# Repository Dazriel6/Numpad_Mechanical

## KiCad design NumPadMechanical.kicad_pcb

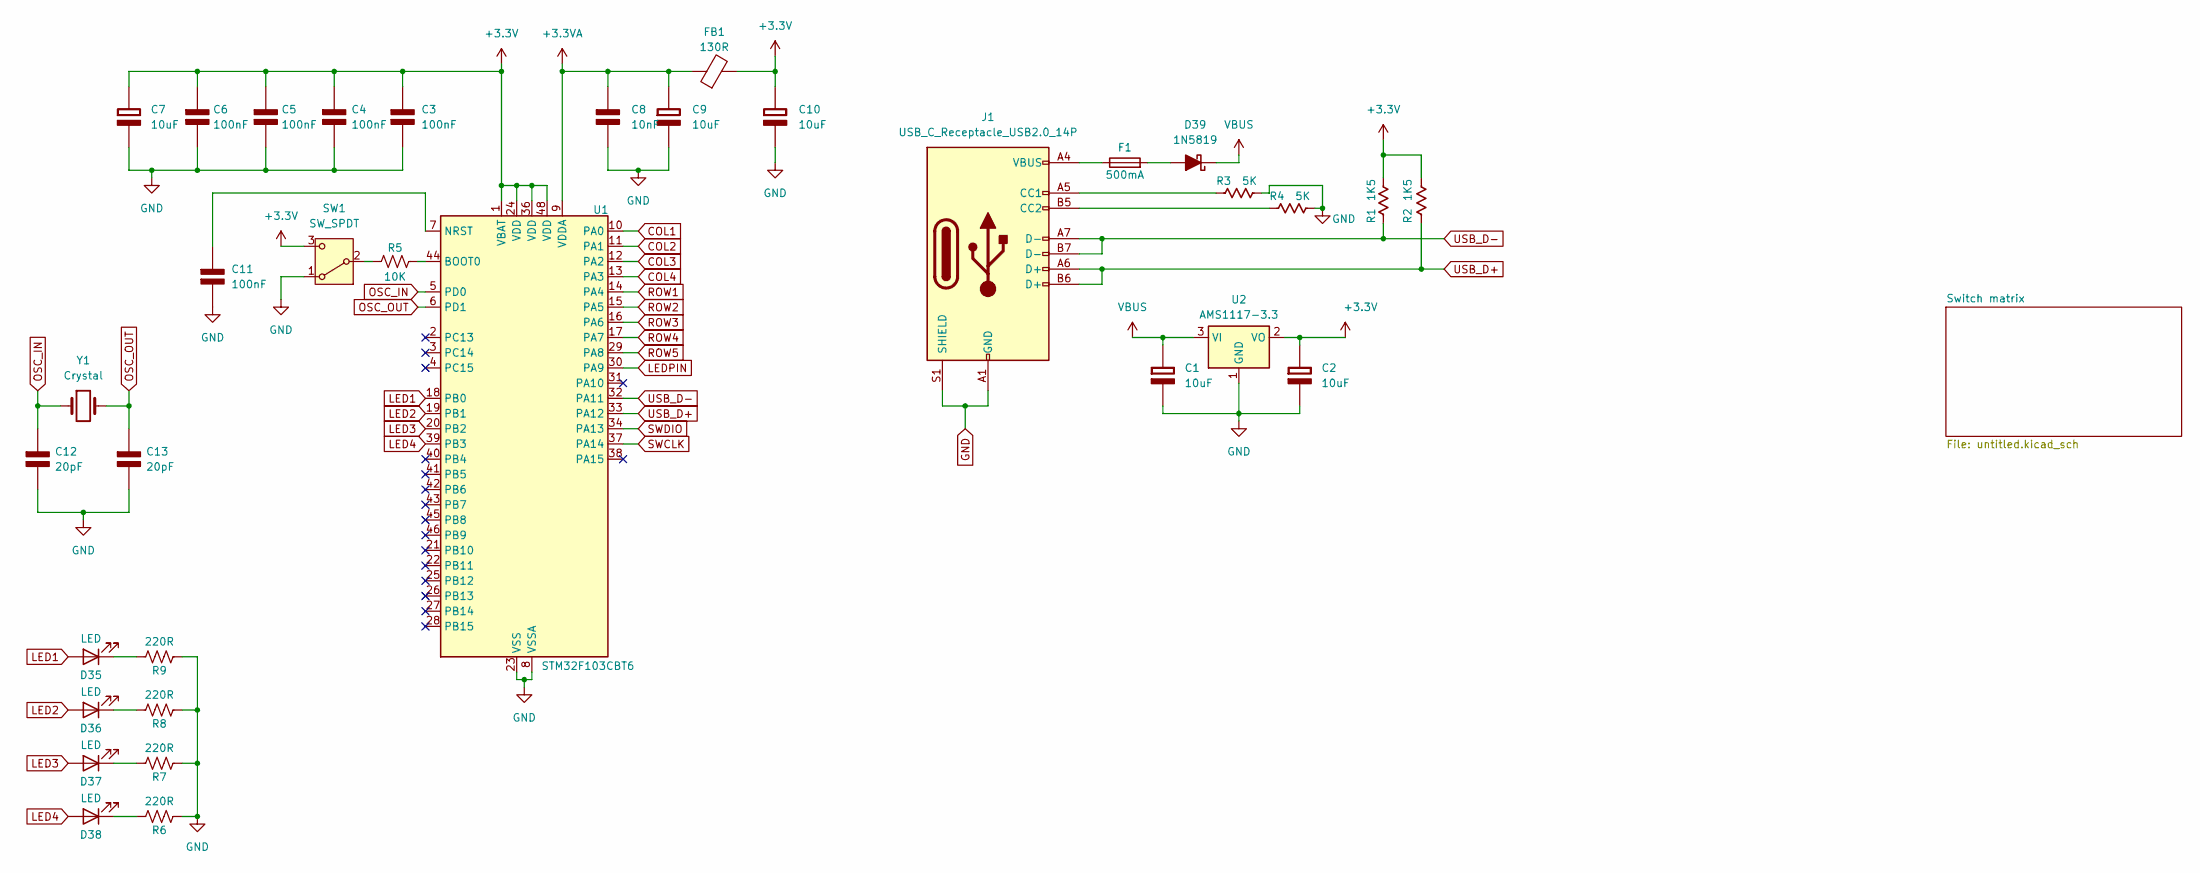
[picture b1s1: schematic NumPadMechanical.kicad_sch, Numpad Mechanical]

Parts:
C1, C2, C7, C9, C10: 10uF; C_0603_1608Metric; Rating V
C3, C4, C5, C6, C11: 100nF; C_0603_1608Metric_Pad1.08x0.95mm_HandSolder; Rating V
C8: 10nF; C_0603_1608Metric; Rating V
C12, C13: 20pF; C_0603_1608Metric_Pad1.08x0.95mm_HandSolder; Rating V
D35, D36, D37, D38: LED; LED_0603_1608Metric
D39: 1N5819; D_SOD-123_A
F1: 500mA; Fuse_0603_1608Metric
FB1: 130R; L_0603_1608Metric
J1: USB_C_Receptacle_USB2.0_14P; USB_C_Receptacle_XKB_U262-16XN-4BVC11
R1, R2: 1K5; R_0603_1608Metric
R3, R4: 5K; R_0603_1608Metric
R5: 10K; R_0603_1608Metric
R6, R7, R8, R9: 220R; R_0603_1608Metric
SW1: SW_SPDT; SW_Slide_SPDT_Straight_CK_OS102011MS2Q
U1: STM32F103CBT6; LQFP-48_7x7mm_P0.5mm
U2: AMS1117-3.3; SOT-223-3_TabPin2
Y1: Crystal; Crystal_SMD_HC49-SD

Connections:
+3.3V: C2.1 (+), C3.1 (+), C4.1 (+), C5.1 (+), C6.1 (+), C7.1 (+), C10.1 (+), FB1.2, R1.2, R2.2, SW1.3 (C), U1.1 (VBAT), U1.24 (VDD), U1.36 (VDD), U1.48 (VDD), U2.2 (VO)
+3.3VA: C8.1 (+), C9.1 (+), FB1.1, U1.9 (VDDA)
COL1: U1.10 (PA0); also elsewhere on the board
COL2: U1.11 (PA1); also elsewhere on the board
COL3: U1.12 (PA2); also elsewhere on the board
COL4: U1.13 (PA3); also elsewhere on the board
GND: C1.2 (-), C2.2 (-), C3.2 (-), C4.2 (-), C5.2 (-), C6.2 (-), C7.2 (-), C8.2 (-), C9.2 (-), C10.2 (-), C11.2 (-), C12.2 (-), C13.2 (-), J1.A1 (GND), J1.A12 (GND), J1.B1 (GND), J1.B12 (GND), J1.S1 (SHIELD), R3.2, R4.2, R6.2, R7.2, R8.2, R9.2, SW1.1 (A), U1.8 (VSSA), U1.23 (VSS), U1.35 (VSS), U1.47 (VSS), U2.1 (GND); also elsewhere on the board
LED1: D35.2 (A), U1.18 (PB0)
LED2: D36.2 (A), U1.19 (PB1)
LED3: D37.2 (A), U1.20 (PB2)
LED4: D38.2 (A), U1.39 (PB3)
LEDPIN: U1.30 (PA9); also elsewhere on the board
unnamed: C11.1 (+), U1.7 (NRST)
unnamed: D35.1 (K), R9.1
unnamed: D36.1 (K), R8.1
unnamed: D37.1 (K), R7.1
unnamed: D38.1 (K), R6.1
unnamed: D39.2 (A), F1.2
unnamed: F1.1, J1.A4 (VBUS), J1.A9 (VBUS), J1.B4 (VBUS), J1.B9 (VBUS)
unnamed: J1.A5 (CC1), R3.1
unnamed: J1.B5 (CC2), R4.1
unnamed: R5.2, SW1.2 (B)
unnamed: R5.1, U1.44 (BOOT0)
OSC_IN: C12.1 (+), U1.5 (PD0), Y1.1
OSC_OUT: C13.1 (+), U1.6 (PD1), Y1.2
ROW1: U1.14 (PA4); also elsewhere on the board
ROW2: U1.15 (PA5); also elsewhere on the board
ROW3: U1.16 (PA6); also elsewhere on the board
ROW4: U1.17 (PA7); also elsewhere on the board
ROW5: U1.29 (PA8); also elsewhere on the board
SWCLK: U1.37 (PA14)
SWDIO: U1.34 (PA13)
USB_D+: J1.A6 (D+), J1.B6 (D+), R2.1, U1.33 (PA12)
USB_D-: J1.A7 (D-), J1.B7 (D-), R1.1, U1.32 (PA11)
VBUS: C1.1 (+), D39.1 (K), U2.3 (VI)

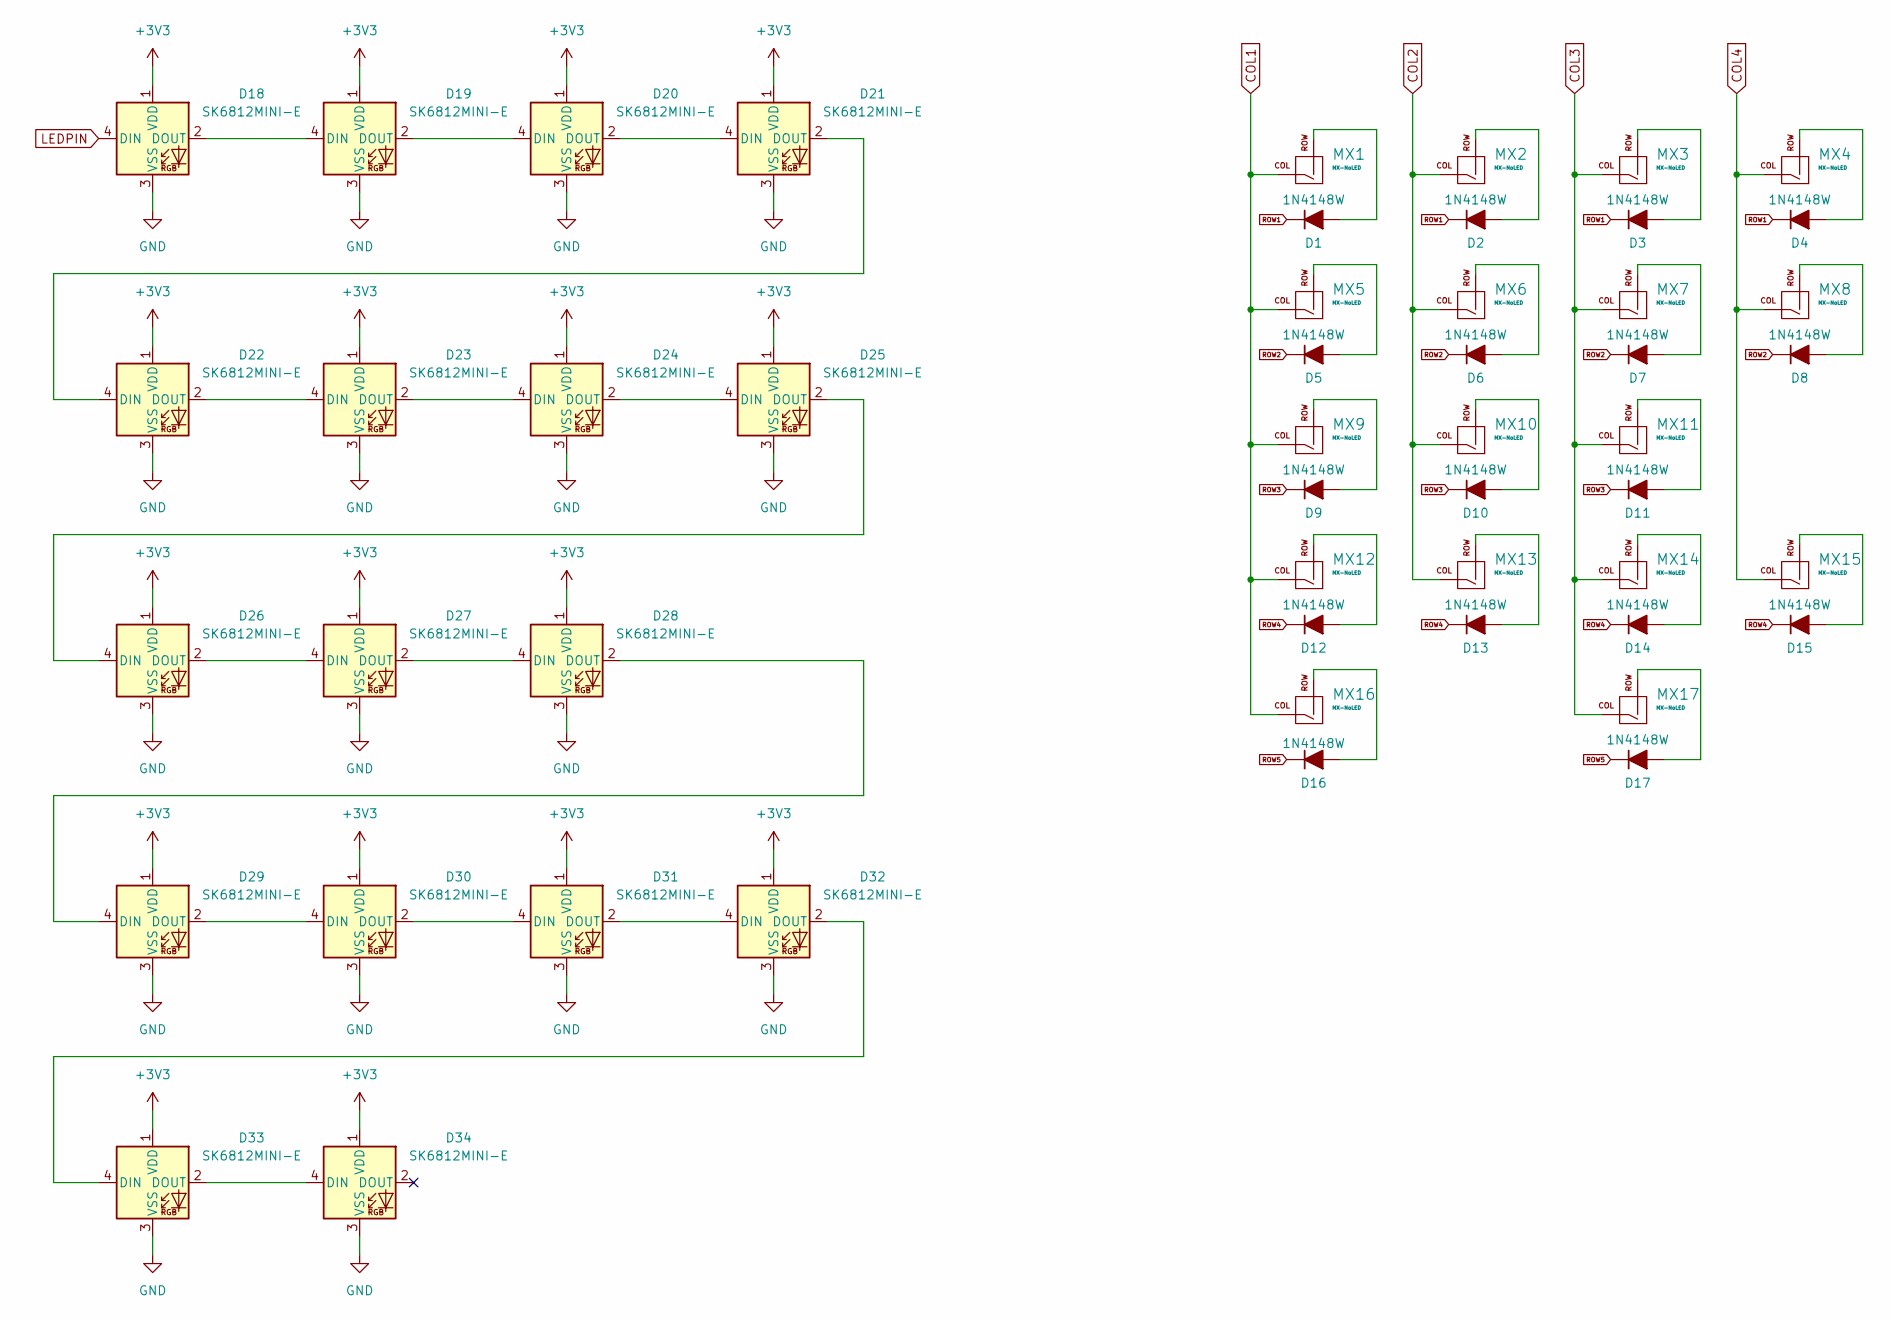
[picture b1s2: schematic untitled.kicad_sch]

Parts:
D1, D2, D3, D4, D5, D6, D7, D8, D9, D10, D11, D12, D13, D14, D15, D16, D17: 1N4148W; D_SOD-123_A
D18, D19, D20, D21, D22, D23, D24, D25, D26, D27, D28, D29, D30, D31, D32, D33, D34: SK6812MINI-E; MX_SK6812MINI-E
MX1, MX2, MX3, MX4, MX5, MX6, MX7, MX9, MX10, MX11, MX12, MX13, MX14, MX17: MX-NoLED; MX-1U-NoLED
MX8, MX15: MX-NoLED; MX-Alps-Hybrid-2U-Vertical
MX16: MX-NoLED; MX-2U-NoLED

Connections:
+3V3: D18.1 (VDD), D19.1 (VDD), D20.1 (VDD), D21.1 (VDD), D22.1 (VDD), D23.1 (VDD), D24.1 (VDD), D25.1 (VDD), D26.1 (VDD), D27.1 (VDD), D28.1 (VDD), D29.1 (VDD), D30.1 (VDD), D31.1 (VDD), D32.1 (VDD), D33.1 (VDD), D34.1 (VDD)
COL1: MX1.1 (COL), MX5.1 (COL), MX9.1 (COL), MX12.1 (COL), MX16.1 (COL); also elsewhere on the board
COL2: MX2.1 (COL), MX6.1 (COL), MX10.1 (COL), MX13.1 (COL); also elsewhere on the board
COL3: MX3.1 (COL), MX7.1 (COL), MX11.1 (COL), MX14.1 (COL), MX17.1 (COL); also elsewhere on the board
COL4: MX4.1 (COL), MX8.1 (COL), MX15.1 (COL); also elsewhere on the board
GND: D18.3 (VSS), D19.3 (VSS), D20.3 (VSS), D21.3 (VSS), D22.3 (VSS), D23.3 (VSS), D24.3 (VSS), D25.3 (VSS), D26.3 (VSS), D27.3 (VSS), D28.3 (VSS), D29.3 (VSS), D30.3 (VSS), D31.3 (VSS), D32.3 (VSS), D33.3 (VSS), D34.3 (VSS); also elsewhere on the board
LEDPIN: D18.4 (DIN); also elsewhere on the board
unnamed: D1.2 (A), MX1.2 (ROW)
unnamed: D2.2 (A), MX2.2 (ROW)
unnamed: D3.2 (A), MX3.2 (ROW)
unnamed: D4.2 (A), MX4.2 (ROW)
unnamed: D5.2 (A), MX5.2 (ROW)
unnamed: D6.2 (A), MX6.2 (ROW)
unnamed: D7.2 (A), MX7.2 (ROW)
unnamed: D8.2 (A), MX8.2 (ROW)
unnamed: D9.2 (A), MX9.2 (ROW)
unnamed: D10.2 (A), MX10.2 (ROW)
unnamed: D11.2 (A), MX11.2 (ROW)
unnamed: D12.2 (A), MX12.2 (ROW)
unnamed: D13.2 (A), MX13.2 (ROW)
unnamed: D14.2 (A), MX14.2 (ROW)
unnamed: D15.2 (A), MX15.2 (ROW)
unnamed: D16.2 (A), MX16.2 (ROW)
unnamed: D17.2 (A), MX17.2 (ROW)
unnamed: D18.2 (DOUT), D19.4 (DIN)
unnamed: D19.2 (DOUT), D20.4 (DIN)
unnamed: D20.2 (DOUT), D21.4 (DIN)
unnamed: D21.2 (DOUT), D22.4 (DIN)
unnamed: D22.2 (DOUT), D23.4 (DIN)
unnamed: D23.2 (DOUT), D24.4 (DIN)
unnamed: D24.2 (DOUT), D25.4 (DIN)
unnamed: D25.2 (DOUT), D26.4 (DIN)
unnamed: D26.2 (DOUT), D27.4 (DIN)
unnamed: D27.2 (DOUT), D28.4 (DIN)
unnamed: D28.2 (DOUT), D29.4 (DIN)
unnamed: D29.2 (DOUT), D30.4 (DIN)
unnamed: D30.2 (DOUT), D31.4 (DIN)
unnamed: D31.2 (DOUT), D32.4 (DIN)
unnamed: D32.2 (DOUT), D33.4 (DIN)
unnamed: D33.2 (DOUT), D34.4 (DIN)
ROW1: D1.1 (K), D2.1 (K), D3.1 (K), D4.1 (K); also elsewhere on the board
ROW2: D5.1 (K), D6.1 (K), D7.1 (K), D8.1 (K); also elsewhere on the board
ROW3: D9.1 (K), D10.1 (K), D11.1 (K); also elsewhere on the board
ROW4: D12.1 (K), D13.1 (K), D14.1 (K), D15.1 (K); also elsewhere on the board
ROW5: D16.1 (K), D17.1 (K); also elsewhere on the board

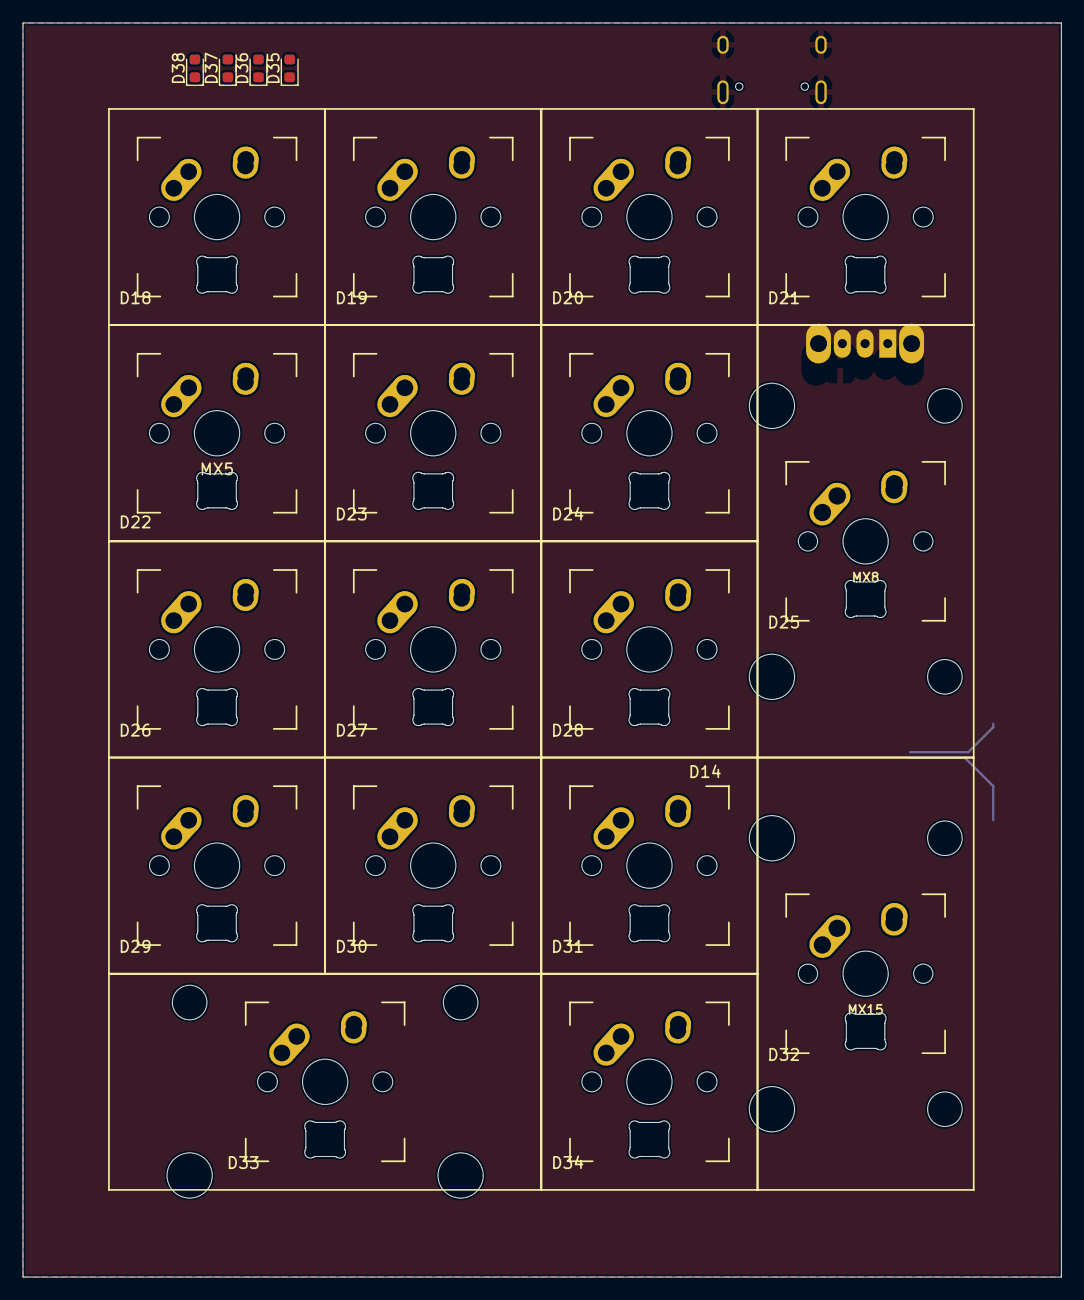
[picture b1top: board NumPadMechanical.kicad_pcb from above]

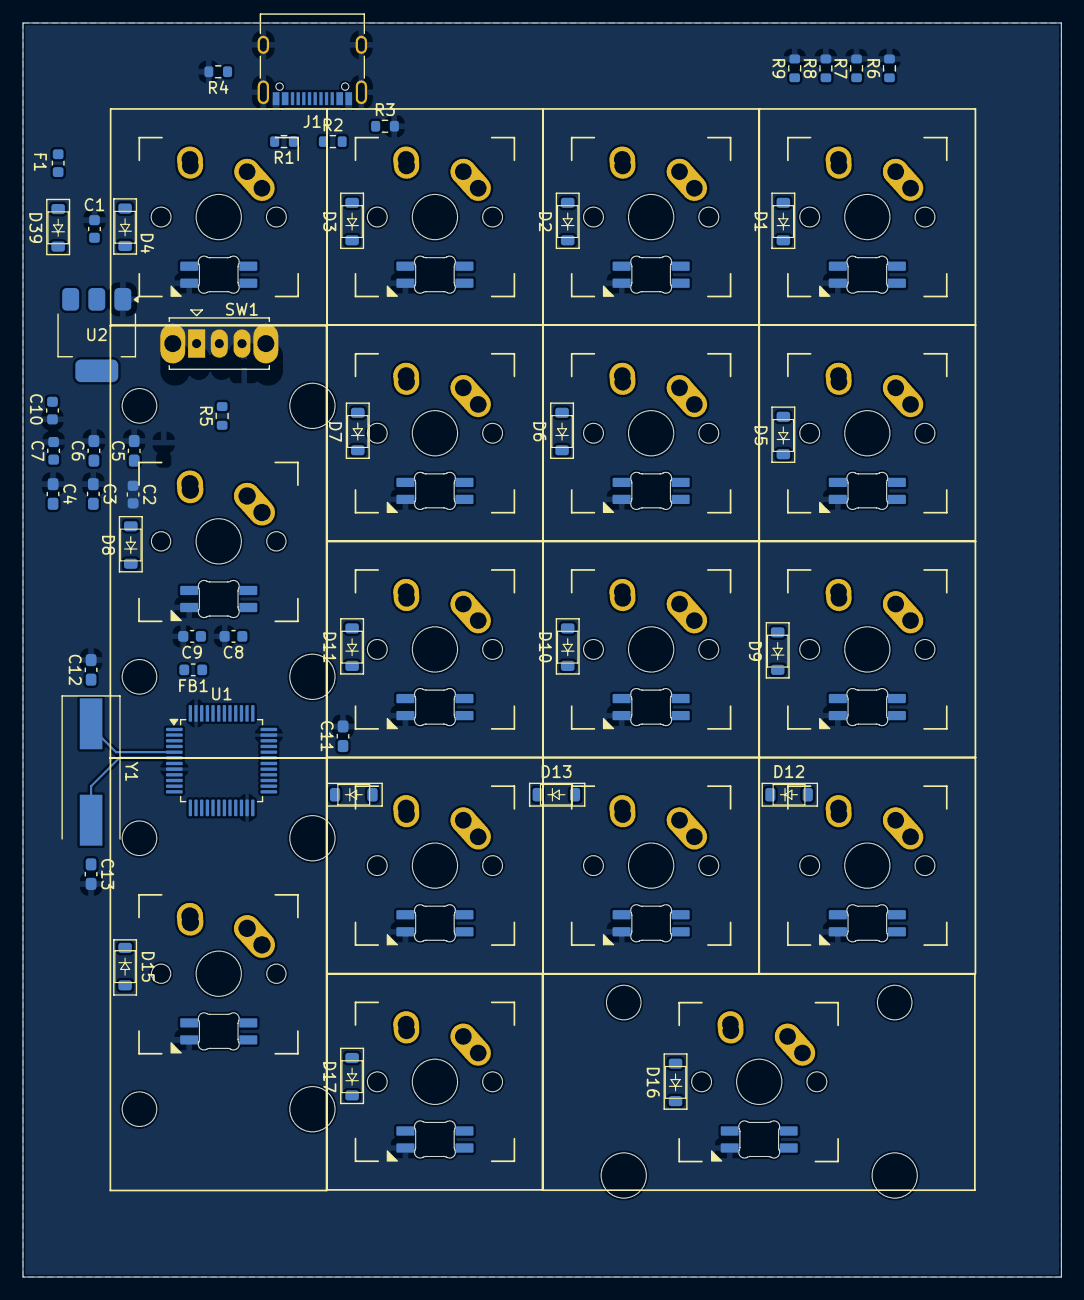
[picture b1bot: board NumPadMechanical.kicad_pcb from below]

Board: 2 copper layers, 91.5 x 110.4 mm, 85 parts (47 on the bottom side), 67 nets.

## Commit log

2024-06-03 Primer commit, archivos generados
2024-06-03 Se agrega la matriz de switches al esquematico
2024-06-04 Se añaden diodos a la matriz de switches, se agrega conector usb y se coloca su cableado
2024-06-04 Se modifican huellas de dispositivos y se agregan modelos 3d en algunas de las huellas
2024-06-05 Agregados capacitores de acoplamiento y regulador de 3v3
2024-06-05 Añadido gitignore y modificaciones en el esquematico
2024-06-05 ignore modificado
2024-06-06 Agregado cristal oscilador y corregido el conector usb, se agregan footprints de algunos dispositivos
2024-06-06 Modificado el esquematico finalizando conexiones, se añaden leds rgb y de señalizacion, se agregan footprints de todos los elementos faltantes y se realiza acomodo de pcb preliminar
2024-06-07 Se hacen modificaciones en la pcb acomodando los dispositivos y se agrega tierra comun en ambos lados de la placa
